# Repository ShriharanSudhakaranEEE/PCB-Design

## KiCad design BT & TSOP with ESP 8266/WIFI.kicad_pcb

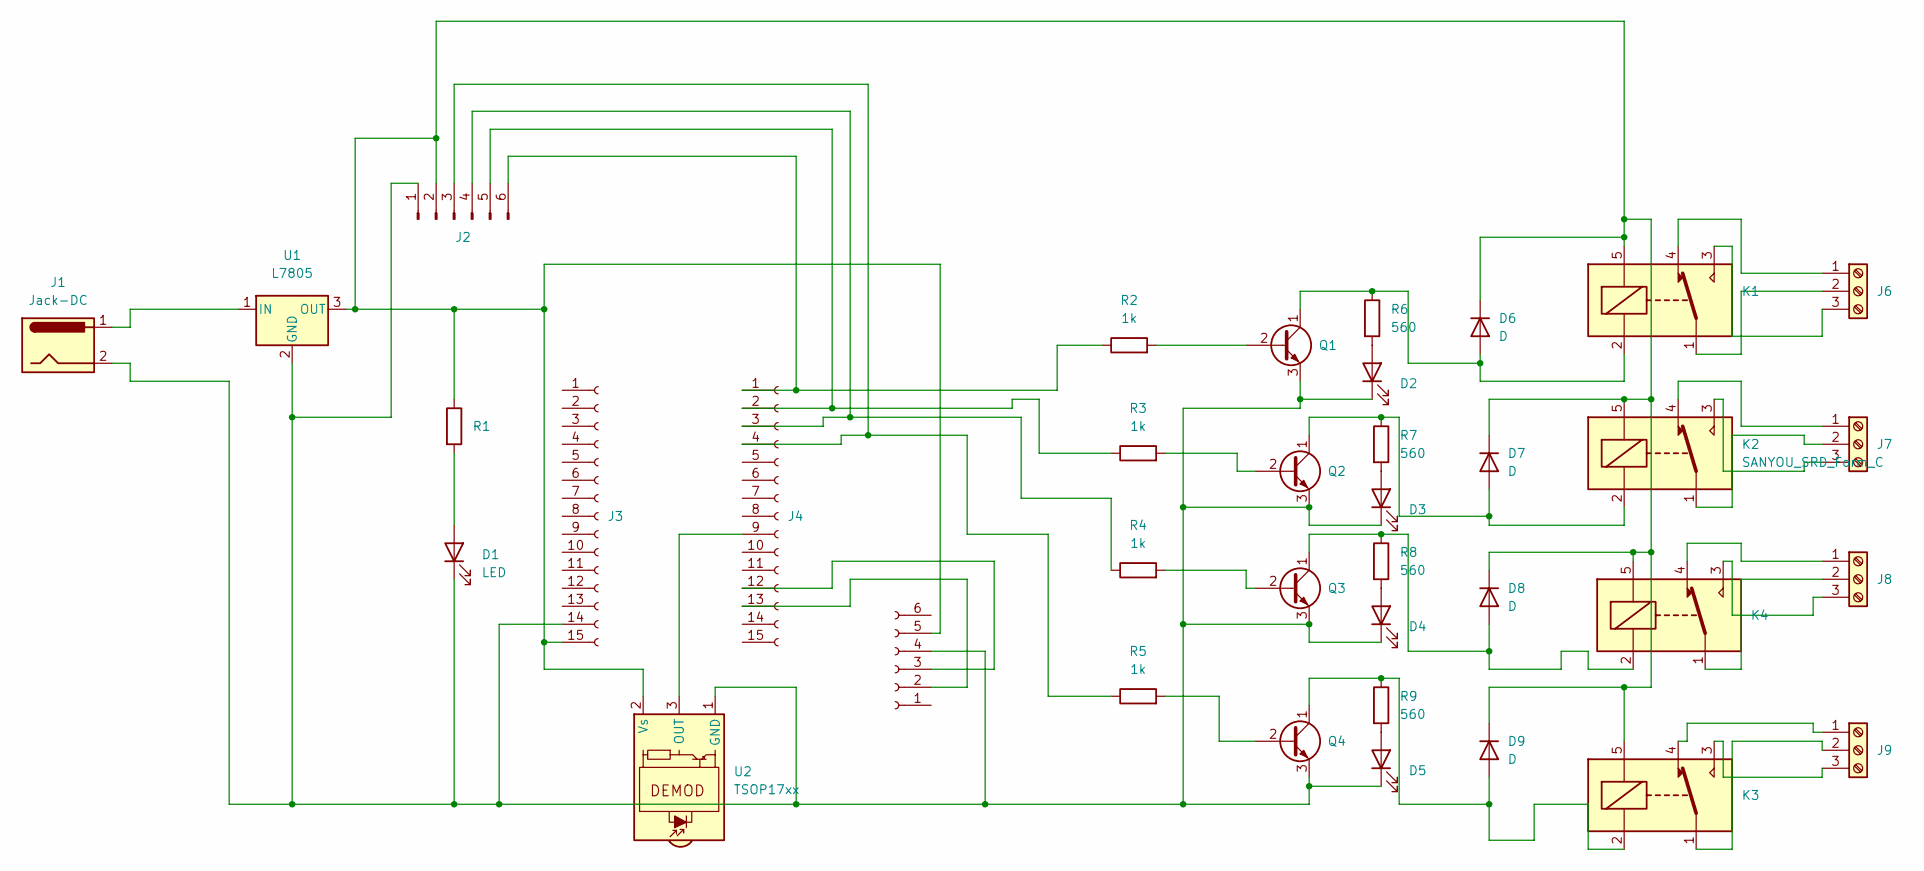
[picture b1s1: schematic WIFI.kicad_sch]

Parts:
D1, D2, D3, D4, D5: LED; LED_D5.0mm_Clear
D6, D7, D8, D9: D; D_DO-41_SOD81_P10.16mm_Horizontal
J1: Jack-DC; BarrelJack_Horizontal
J2: Conn_01x06_Male; PinSocket_1x06_P2.54mm_Vertical
J3, J4: Conn_01x15_Female; PinHeader_1x15_P2.54mm_Vertical
J5: Conn_01x06_Female; PinSocket_1x06_P2.54mm_Vertical
J6, J7, J8, J9: Screw_Terminal_01x03; TerminalBlock_Altech_AK300-3_P5.00mm
K1, K2, K3, K4: SANYOU_SRD_Form_C; Relay_SPDT_SANYOU_SRD_Series_Form_C
Q1, Q2, Q3, Q4: BC547; TO-92_Inline_Wide
R1: R; R_Axial_DIN0207_L6.3mm_D2.5mm_P10.16mm_Horizontal
R2, R3, R4, R5: 1k; R_Axial_DIN0207_L6.3mm_D2.5mm_P10.16mm_Horizontal
R6, R7, R8, R9: 560; R_Axial_DIN0207_L6.3mm_D2.5mm_P10.16mm_Horizontal
U1: L7805; TO-220-3_Vertical
U2: TSOP17xx; Vishay_CAST-3Pin

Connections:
unnamed: D1.1 (K), D2.1 (K), D3.1 (K), D4.1 (K), D5.1 (K), J1.2, J2.1, J3.14, J5.4, Q1.3 (E), Q2.3 (E), Q3.3 (E), Q4.3 (E), U1.2 (GND), U2.1 (GND)
unnamed: D1.2 (A), R1.2
unnamed: D2.2 (A), R6.2
unnamed: D3.2 (A), R7.2
unnamed: D4.2 (A), R8.2
unnamed: D5.2 (A), R9.2
unnamed: D6.2 (A), K1.2, Q1.1 (C), R6.1
unnamed: D7.2 (A), K2.2, Q2.1 (C), R7.1
unnamed: D8.2 (A), K4.2, Q3.1 (C), R8.1
unnamed: D9.2 (A), K3.2, Q4.1 (C), R9.1
unnamed: J1.1, U1.1 (IN)
unnamed: D6.1 (K), D7.1 (K), D8.1 (K), D9.1 (K), J2.2, J3.15, J5.5, K1.5, K2.5, K3.5, K4.5, R1.1, U1.3 (OUT), U2.2 (Vs)
unnamed: J2.3, J4.4, R5.1
unnamed: J2.4, J4.3, R4.1
unnamed: J2.5, J4.2, R3.1
unnamed: J2.6, J4.1, R2.1
unnamed: J4.9, U2.3 (OUT)
unnamed: J4.12, J5.3
unnamed: J4.13, J5.2
unnamed: J6.1, K1.4
unnamed: J6.2, K1.1
unnamed: J6.3, K1.3
unnamed: J7.1, K2.4
unnamed: J7.2, K2.1
unnamed: J7.3, K2.3
unnamed: J8.1, K4.4
unnamed: J8.2, K4.1
unnamed: J8.3, K4.3
unnamed: J9.1, K3.4
unnamed: J9.2, K3.1
unnamed: J9.3, K3.3
unnamed: Q1.2 (B), R2.2
unnamed: Q2.2 (B), R3.2
unnamed: Q3.2 (B), R4.2
unnamed: Q4.2 (B), R5.2

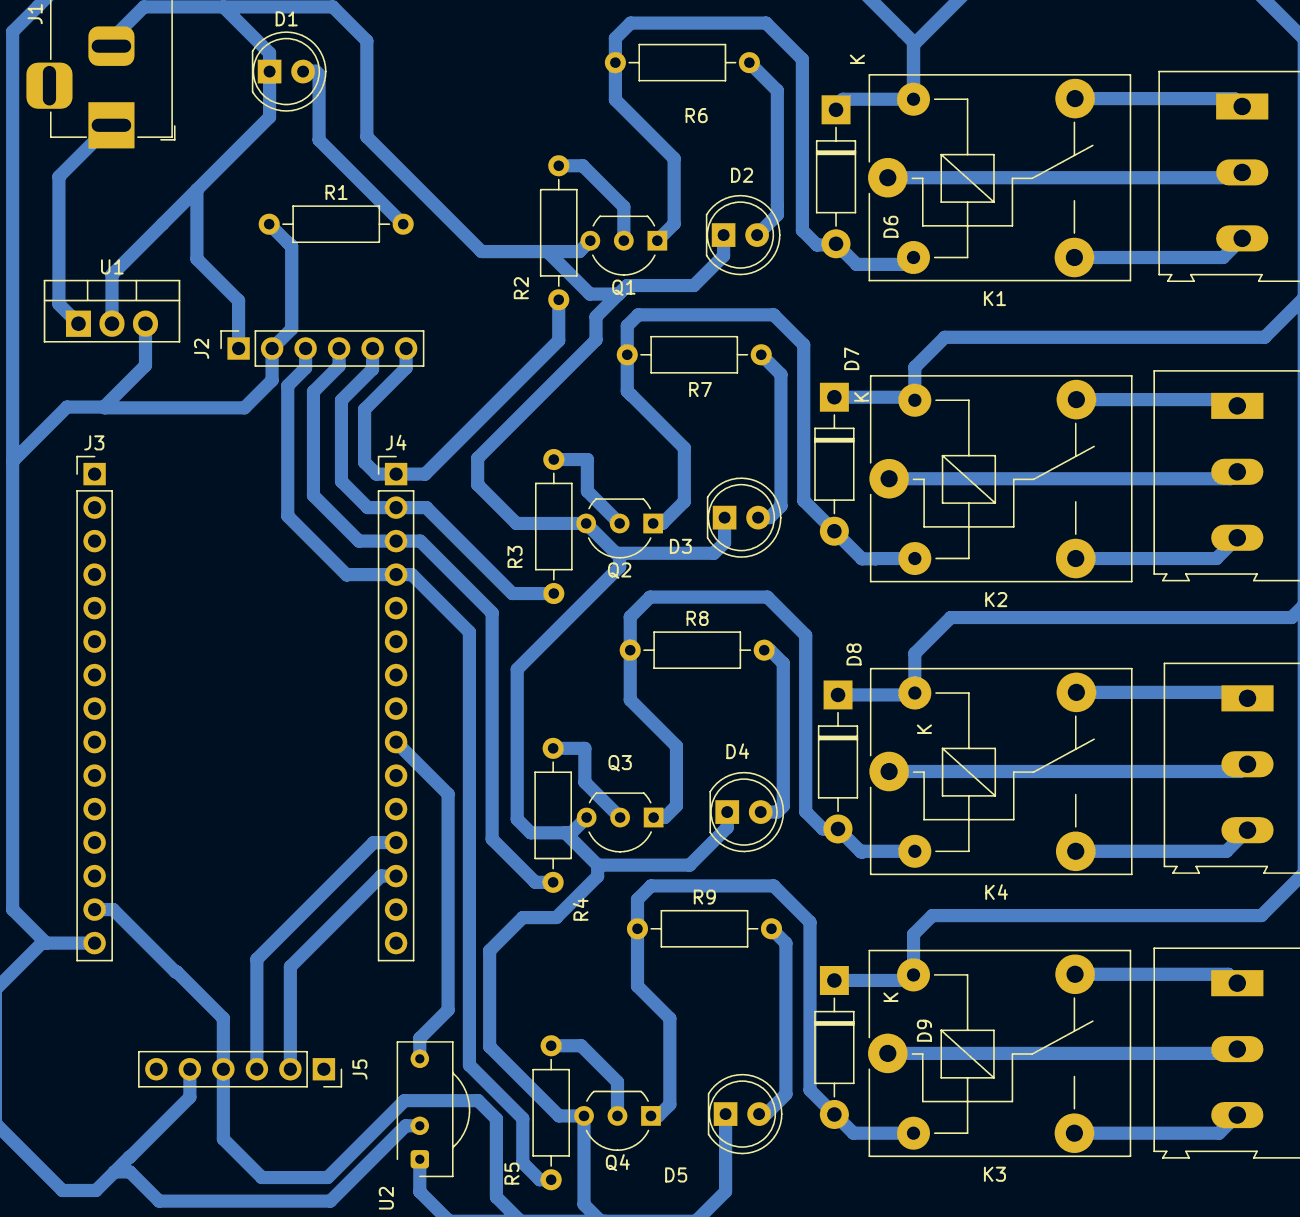
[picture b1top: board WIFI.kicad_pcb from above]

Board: 2 copper layers, 37 parts (0 on the bottom side), 35 nets.
